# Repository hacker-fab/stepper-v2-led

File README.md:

# stepper-v2-led
Hacker Fab V2 Stepper UV LED PCB

UV LED module for the [Stepper V2](https://docs.hackerfab.org/home/fab-toolkit/patterning/lithography-stepper-v2-build-work-in-progress#bill-of-materials)

Files imported from [Google drive](https://drive.google.com/drive/u/1/folders/1X3nmuruO58prPQBm8DrWUhfM-LNq0qWm)

Supported projectors:
  * DLPDLCR471TPEVM: the classic V2 projector
  * DLP4710EVM-LC: experimental projector due to part shortage

LED compatibility:

| Pin      | DLPDLCR471TPEVM | DLP4710EVM-LC |
| -------- | --------------- | ------- |
| 10       | N/C             | Common   |
| 9        | N/C             | Common   |
| 8        | LED+            | Common   |
| 7        | LED+            | Common   |
| 6        | LED+            | Common   |
| 5        | LED+            | LED1+   |
| 4        | LED-            | LED1+   |
| 3        | LED-            | LED1+   |
| 2        | LED-            | LED2+   |
| 1        | LED-            | LED2+   |

"You can order it through your PCB manufacturer of choice (we used JLCPCB). However, note that the PCB is copper core. This is because the LEDs draw several amps of current in operation. To ensure that the PCB doesn't melt, you should use copper core to facilitate better heat flow."

"When ordering the PCB, the manufacturer might send you an email asking about a missing heatsink file. In this case, please respond that this project does not include a direct heatsink, as the copper core PCB itself is designed to handle the thermal management."

DLPDLCR471TPEVM (4 LED) BOM:

| Vendor    | Model | Price each (2025) | Quantity | Link |
| -------- | ------- | ------- | ------- | ------- |
|  	Lumileds |  L1F3-U400200012000  | $10.50   |  4  |  [Digikey](https://www.digikey.com/en/products/detail/lumileds/L1F3-U400200012000/7389568)  |
| Molex  |  0874371043  | $0.71   |  1  |  [Digikey](https://www.digikey.com/en/products/detail/molex/0874371043/717647)  |

Notes:
* DLP4710EVM-LC
  * Instead use [Molex 0874381043](https://www.digikey.com/en/products/detail/molex/0874381043/699154)
  * [FOSSF Silicon notes](https://docs.google.com/document/d/1Yg9_48nFprNLK36mjKuTRpAcMww_u_pMMim5-wJe3lg/edit?tab=t.0#heading=h.3c9frve8h9fi)
* Connectors mate with [Molex 0874391000](https://www.digikey.com/en/products/detail/molex/0874391000/561773)
  * Pins: suggest [Molex 874210000](https://www.digikey.com/en/products/detail/molex/0874210000/2037270)

TODO:
* Organize outputs / "history"
  * Which are 4 vs 6 LED designs?
* Create gerber release files
* Port existing files to KiCAD?
* Add images to docs
* DLP4710EVM-LC
  * Measure voltage on existing blue LEDs
    * Are these driven with lower voltage?
  * Make new PCB
  * Clean BOM instructions (connector / LEDs)
link a pr
# History

I can't access the [officially linked gerber file](https://drive.google.com/drive/u/1/folders/1DK4DBdWB0b6NKSaRz9XtcY19dkCHzusb)

FIXME: some files look somewhat identical but not vs the timestamps?

Looks like started with 6 LED design and then moved to 4 LED

| Artifact                      | Drive name                         | LEDs | Notes                                |
| ----------------------------- | ---------------------------------- | ---  | ------------------------------------ |
| dlpdlcr471tpevm-led_v1.zip    | Project Outputs for UV_LED.zip     | 6    | "1:49:43 AM On 6/20/2023"            |
| dlpdlcr471tpevm-led_v2.zip    | Project Outputs for UV_LED (2).zip<br>(Project Outputs for UV_LED/)         | 6    | "2:43:13 PM On 6/20/2023"<br>Rounds / enlarges traces            |
| dlpdlcr471tpevm-led_v3.zip    | UV_LED_v2.zip                      | 4    | "6:19:09 PM On 10/3/2023"<br>"Official" file in the instructions? |

Note these two were nearly identical:
* "Project Outputs for UV_LED/": lf line endings. Deleted since redundant + inconsistent
* "Project Outputs for UV_LED (2).zip": cr/lf line endings
* Most have cr/lf line endings

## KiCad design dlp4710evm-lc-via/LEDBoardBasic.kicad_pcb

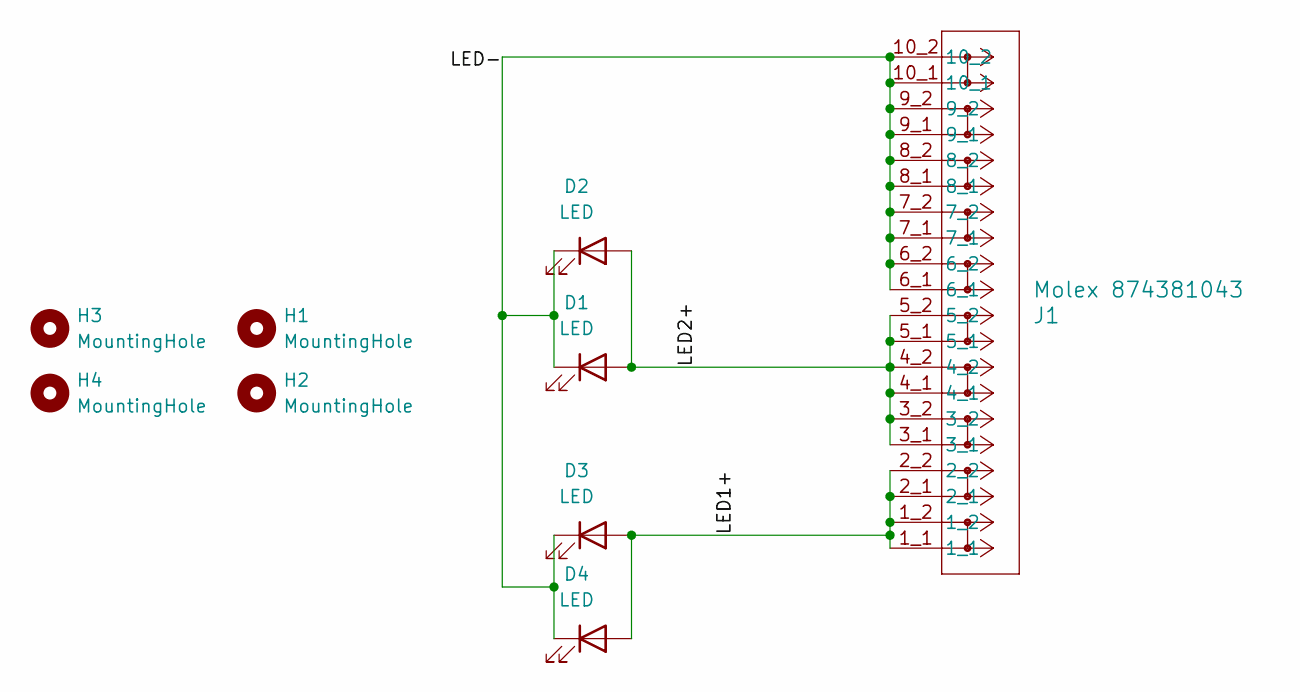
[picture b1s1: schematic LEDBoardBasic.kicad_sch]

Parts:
D1, D2, D3, D4: LED; LED_Cree-XQ
H1, H2: MountingHole; 0dot093_inch_mechanical_hole
H3, H4: MountingHole; 0dot060_inch_mechanical_hole
J1: Molex 874381043; CONN_874380231-SD_10_MOL

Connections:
/LED1+: D3.2 (A), D4.2 (A), J1.1_1, J1.1_2, J1.2_1, J1.2_2
/LED2+: D1.2 (A), D2.2 (A), J1.3_1, J1.3_2, J1.4_1, J1.4_2, J1.5_1, J1.5_2
/LED-: D1.1 (K), D2.1 (K), D3.1 (K), D4.1 (K), J1.6_1, J1.6_2, J1.7_1, J1.7_2, J1.8_1, J1.8_2, J1.9_1, J1.9_2, J1.10_1, J1.10_2

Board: 2 copper layers, 9 parts (0 on the bottom side), 3 nets, no tracks yet.

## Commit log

2025-03-19 Import files from drive verbatim
2025-03-19 Organize / normalize file names
2025-03-19 clean up gerber files
2025-04-02 Added KiCAD Files
    KiCAD files added
2025-04-02 Removed redundant files
    Removed redundant files
2025-04-08 clean up new projector file name
2025-04-08 dlp4710evm-lc-led: clean up / normalize outputs
2025-04-15 Added LEDBoardBasic Files
    An alternative board is now available, titled LEDBoardBasic, which achieves the LED heatsinking through many vias to the back copper of a standard 2 sided FR4 core board
2025-04-15 normalize file names
2025-04-16 dlp4710evm-lc-via_v1 release candidate
2025-04-16 dlp4710evm-lc-via: tweak inconsistent solder mask
2025-04-16 Added footprints
    Added mechanical hole footprints which were missing from project library.
2025-04-16 gerber: fix file name
